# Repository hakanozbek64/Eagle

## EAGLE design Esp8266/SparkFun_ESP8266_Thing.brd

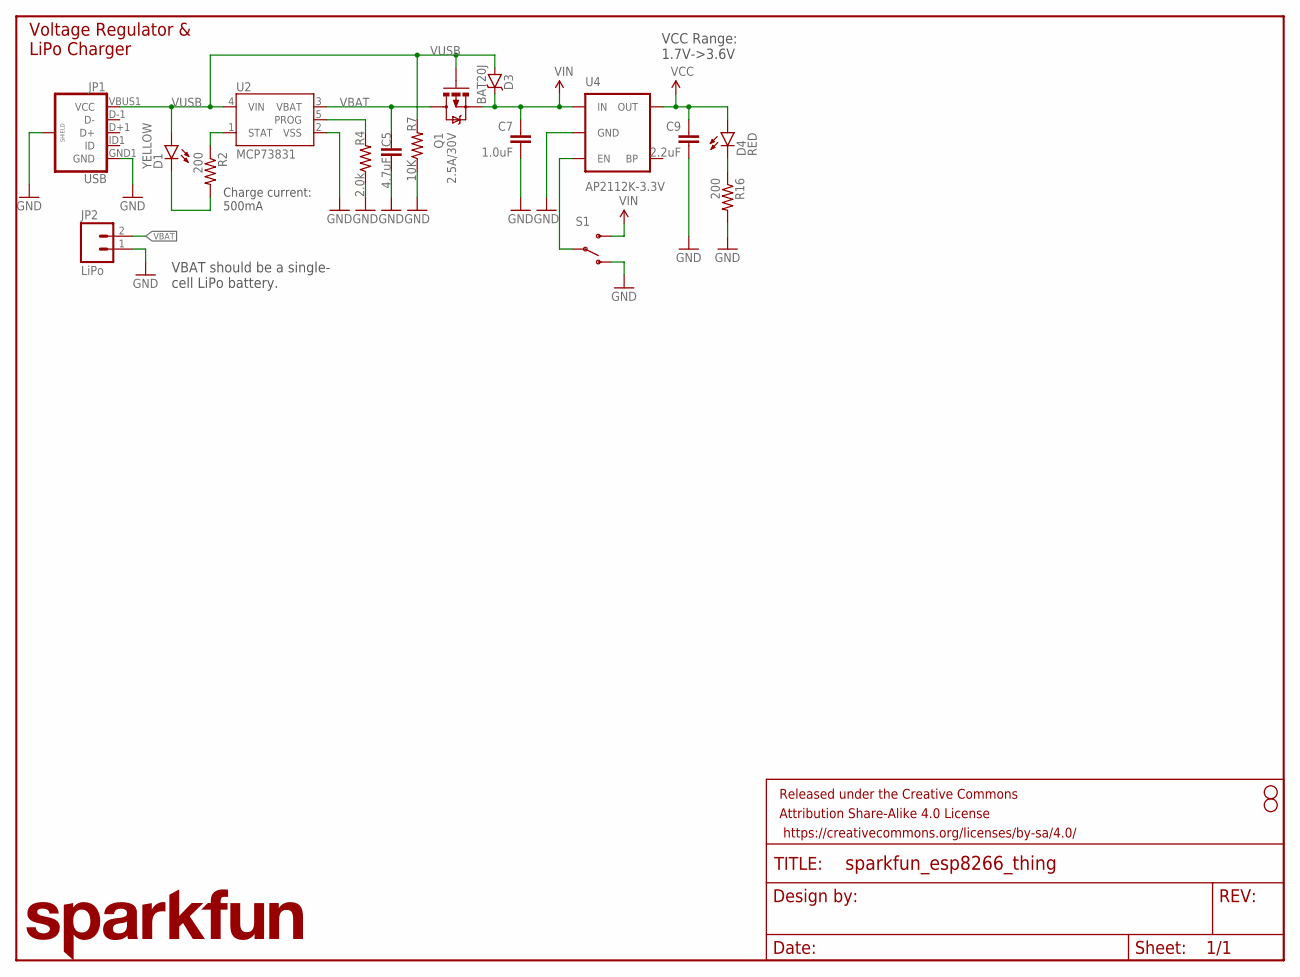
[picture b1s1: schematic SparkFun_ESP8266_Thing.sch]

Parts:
C5: 4.7uF; 0603-CAP
C7: 1.0uF; 0805
C9: 2.2uF; 0603-CAP
D1: YELLOW; LED-0603
D3: BAT20J; SOD-323
D4: RED; LED-0603
FRAME1: FRAME-LETTER; CREATIVE_COMMONS
JP1: USB; USB-B-MICRO-SMD_V03
JP2: LiPo; JST-2-PTH
LOGO1: SFE_LOGO_NAME.2_INCH; SFE_LOGO_NAME_.2
Q1: 2.5A/30V; SOT23-3
R2, R16: 200; 0603-RES
R4: 2.0k; 0603-RES
R7: 10K; 0603-RES
S1: SWITCH-SPDT-SMD-A; SWITCH-SPST-SMD-A
STANDOFF3, STANDOFF4: STAND-OFF
U2: MCP73831; SOT23-5
U4: AP2112K-3.3V; SOT23-5

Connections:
GND: C5.2, C7.2, C9.2, JP1.GND1 (GND), JP1.SHIELD1 (SHIELD), JP1.SHIELD2 (SHIELD), JP1.SHIELD3 (SHIELD), JP2.1, R4.1, R7.1, R16.2, S1.1 (O), U2.2 (VSS), U4.2 (GND)
unnamed: D4.C, R16.1
unnamed: S1.2, U4.3 (EN)
unnamed: R4.2, U2.5 (PROG)
unnamed: D1.C, R2.2
unnamed: R2.1, U2.1 (STAT)
VBAT: C5.1, JP2.2, Q1.3 (D), U2.3 (VBAT)
VCC: C9.1, D4.A, U4.5 (OUT)
VIN: C7.1, D3.C, Q1.2 (S), S1.3 (S), U4.1 (IN)
VUSB: D1.A, D3.A, JP1.VBUS1 (VCC), Q1.1 (G), R7.2, U2.4 (VIN)

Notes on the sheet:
Voltage Regulator & LiPo Charger
VCC Range: 1.7V->3.6V
VBAT should be a single- cell LiPo battery.
Charge current: 500mA

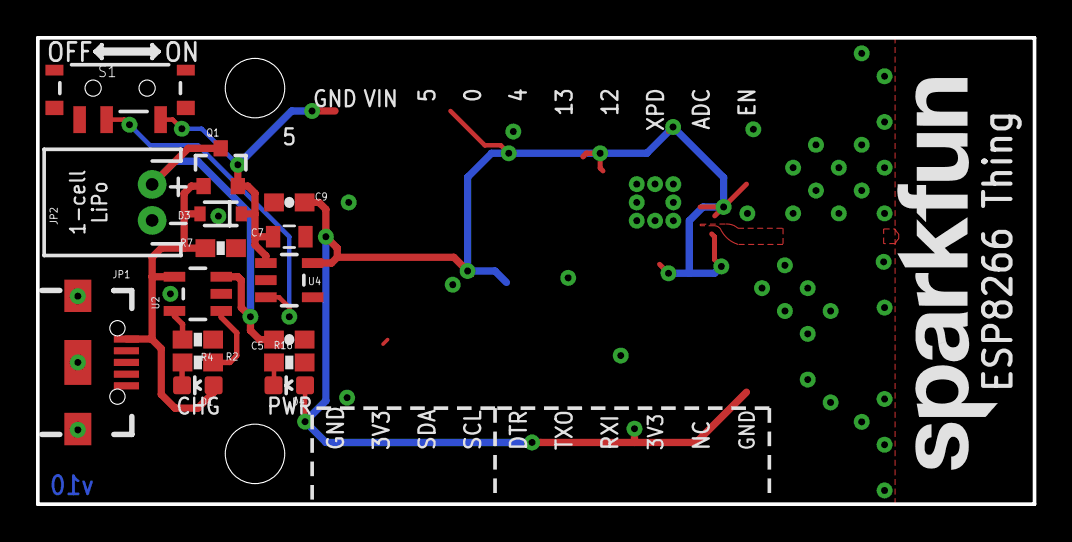
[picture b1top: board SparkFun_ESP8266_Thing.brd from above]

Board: 2 copper layers, 55.4 x 25.9 mm, 21 parts (1 on the bottom side), 10 nets.

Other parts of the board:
LOGO5: SFE_LOGO_NAME.2_INCH; SFE_LOGO_NAME_.2

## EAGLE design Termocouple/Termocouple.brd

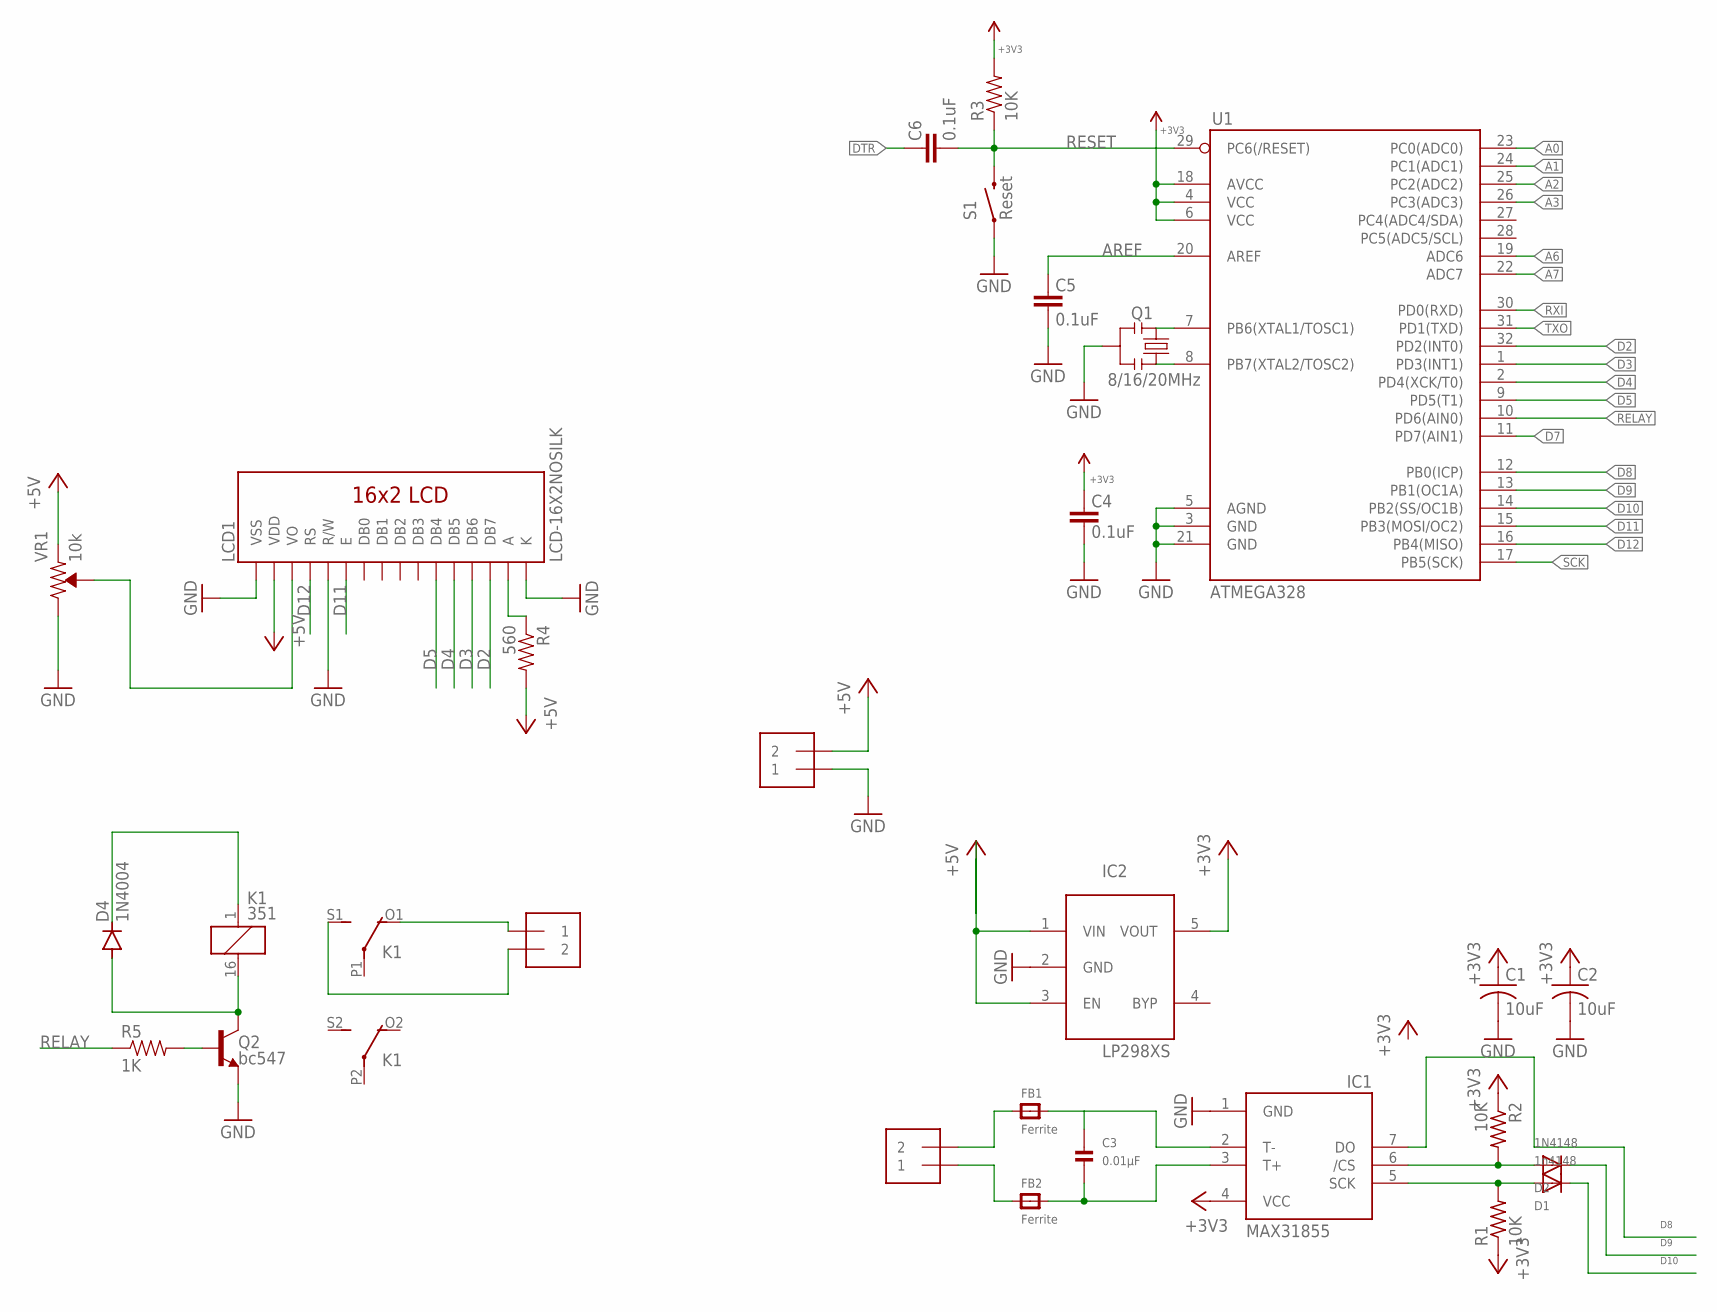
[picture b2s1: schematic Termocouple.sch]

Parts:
C1, C2: 10uF; C0805K
C3: 0.01µF; _0805
C4, C5, C6: 0.1uF; 0603-CAP
D1: 1n4148; SOD-323F
D2: 1N4148; SOD-323F
D4: 1N4004; DO41-10
FB1, FB2: Ferrite; _0805
IC1: MAX31855; SO08
IC2: LP298XS; SOT23-5L
J1, J2, J3: 1X2-3.5MM
K1: 351
LCD1: LCD-16X2NOSILK; LCD-16X2_NOSILK
Q1: 8/16/20MHz; RESONATOR-SMD-1:1
Q2: bc547; SOT23-3
R1, R2: 10K; R0805
R3: 10K; 0805
R4: 560; 0805
R5: 1K; 0805
S1: Reset; TACTILE-SWITCH-SMD-ALT01
U1: ATMEGA328; TQFP32-08
VR1: 10k; TRIMPOT-SMD-3MM-CLOSED

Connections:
+3V3: C1.1, C2.1, C4.2, IC1.4 (VCC), IC2.5 (VOUT), R1.1, R2.1, R3.2, U1.4 (VCC), U1.6 (VCC), U1.18 (AVCC)
+5V: IC2.1 (VIN), IC2.3 (EN), J2.2, LCD1.2 (VDD), R4.2, VR1.1 (CCW)
A0: U1.23 (PC0(ADC0))
A1: U1.24 (PC1(ADC1))
A2: U1.25 (PC2(ADC2))
A3: U1.26 (PC3(ADC3))
A6: U1.19 (ADC6)
A7: U1.22 (ADC7)
AREF: C5.2, U1.20 (AREF)
CS: D2.A, IC1.6 (/CS), R2.2
D2: LCD1.14 (DB7), U1.32 (PD2(INT0))
D3: LCD1.13 (DB6), U1.1 (PD3(INT1))
D4: LCD1.12 (DB5), U1.2 (PD4(XCK/T0))
D5: LCD1.11 (DB4), U1.9 (PD5(T1))
D7: U1.11 (PD7(AIN1))
D8: IC1.7 (DO), U1.12 (PB0(ICP))
D9: D2.C, U1.13 (PB1(OC1A))
D10: D1.C, U1.14 (PB2(SS/OC1B))
D11: LCD1.6 (E), U1.15 (PB3(MOSI/OC2))
D12: LCD1.4 (RS), U1.16 (PB4(MISO))
DTR: C6.2
GND: C1.2, C2.2, C4.1, C5.1, IC1.1 (GND), IC2.2 (GND), J2.1, LCD1.1 (VSS), LCD1.5 (R/W), LCD1.16 (K), Q1.2, Q2.2 (E), S1.1, S1.2 (1), U1.3 (GND), U1.5 (AGND), U1.21 (GND), VR1.3 (CW)
unnamed: FB1.1, J1.2
unnamed: LCD1.15 (A), R4.1
unnamed: LCD1.3 (VO), VR1.2 (WIPER)
unnamed: C3.1, FB1.2, IC1.2 (T-)
unnamed: FB2.1, J1.1
unnamed: C3.2, FB2.2, IC1.3 (T+)
unnamed: Q1.3, U1.8 (PB7(XTAL2/TOSC2))
unnamed: Q1.1, U1.7 (PB6(XTAL1/TOSC1))
unnamed: D4.C, K1.1
unnamed: D4.A, K1.16 (2), Q2.3 (C)
unnamed: Q2.1 (B), R5.2
unnamed: J3.2, K1.S1 (S)
unnamed: J3.1, K1.O1 (O)
RELAY: R5.1, U1.10 (PD6(AIN0))
RESET: C6.1, R3.1, S1.3 (2), S1.4 (2), U1.29 (PC6(/RESET))
RXI: U1.30 (PD0(RXD))
SCK: D1.A, IC1.5 (SCK), R1.2, U1.17 (PB5(SCK))
TXO: U1.31 (PD1(TXD))

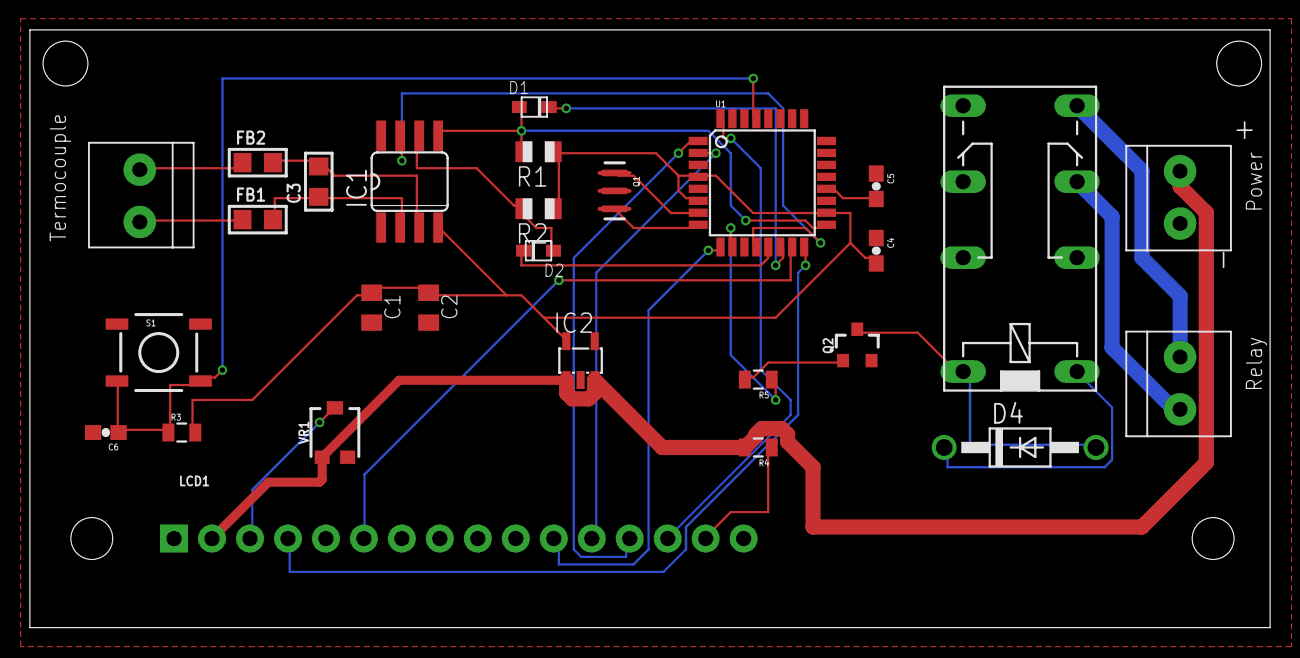
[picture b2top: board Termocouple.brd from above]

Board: 2 copper layers, 82.9 x 40.0 mm, 28 parts (0 on the bottom side), 30 nets.

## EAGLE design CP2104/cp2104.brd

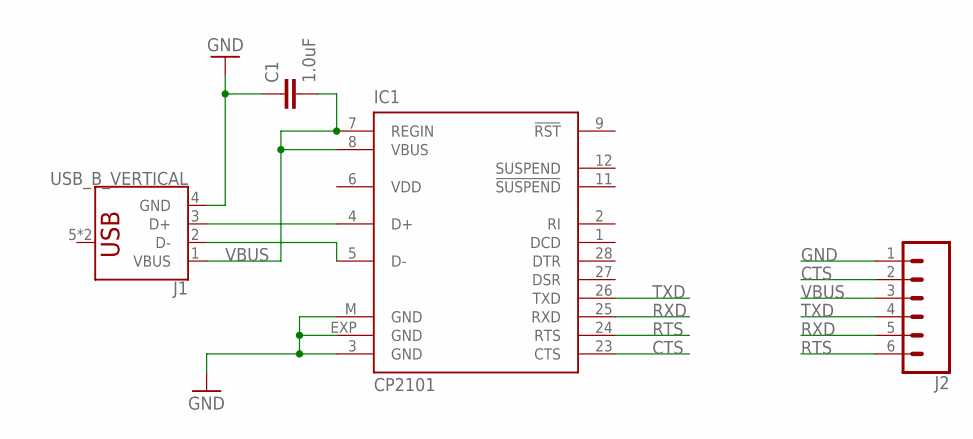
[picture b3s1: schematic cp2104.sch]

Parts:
C1: 1.0uF; 0805
IC1: CP2101; MLP28
J1: USB_B_VERTICAL; USB_B_VERTICAL_PTH
J2: CONN_06NO_SILK_FEMALE_PTH; 1X06_NO_SILK

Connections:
CTS: IC1.23 (CTS), J2.2
GND: C1.1, IC1.3 (GND), IC1.EXP (GND), IC1.M (GND), J1.4 (GND), J2.1
unnamed: IC1.5 (D-), J1.2 (D-)
unnamed: IC1.4 (D+), J1.3 (D+)
RTS: IC1.24 (RTS), J2.6
RXD: IC1.25 (RXD), J2.5
TXD: IC1.26 (TXD), J2.4
VBUS: C1.2, IC1.7 (REGIN), IC1.8 (VBUS), J1.1 (VBUS), J2.3
VDD: IC1.6 (VDD)

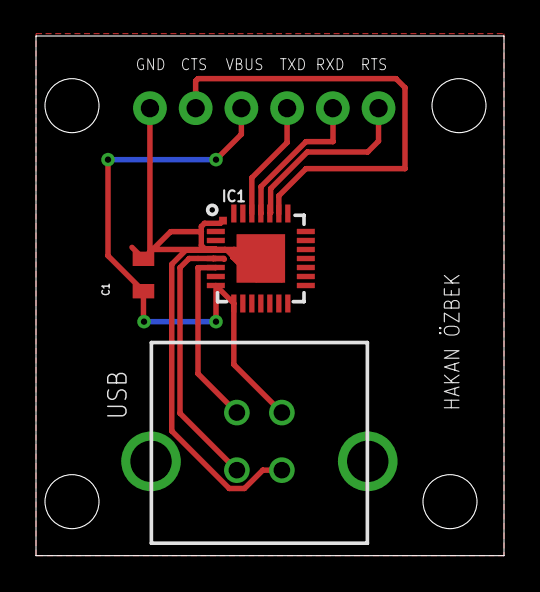
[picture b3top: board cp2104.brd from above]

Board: 2 copper layers, 26.0 x 28.9 mm, 4 parts (0 on the bottom side), 8 nets.

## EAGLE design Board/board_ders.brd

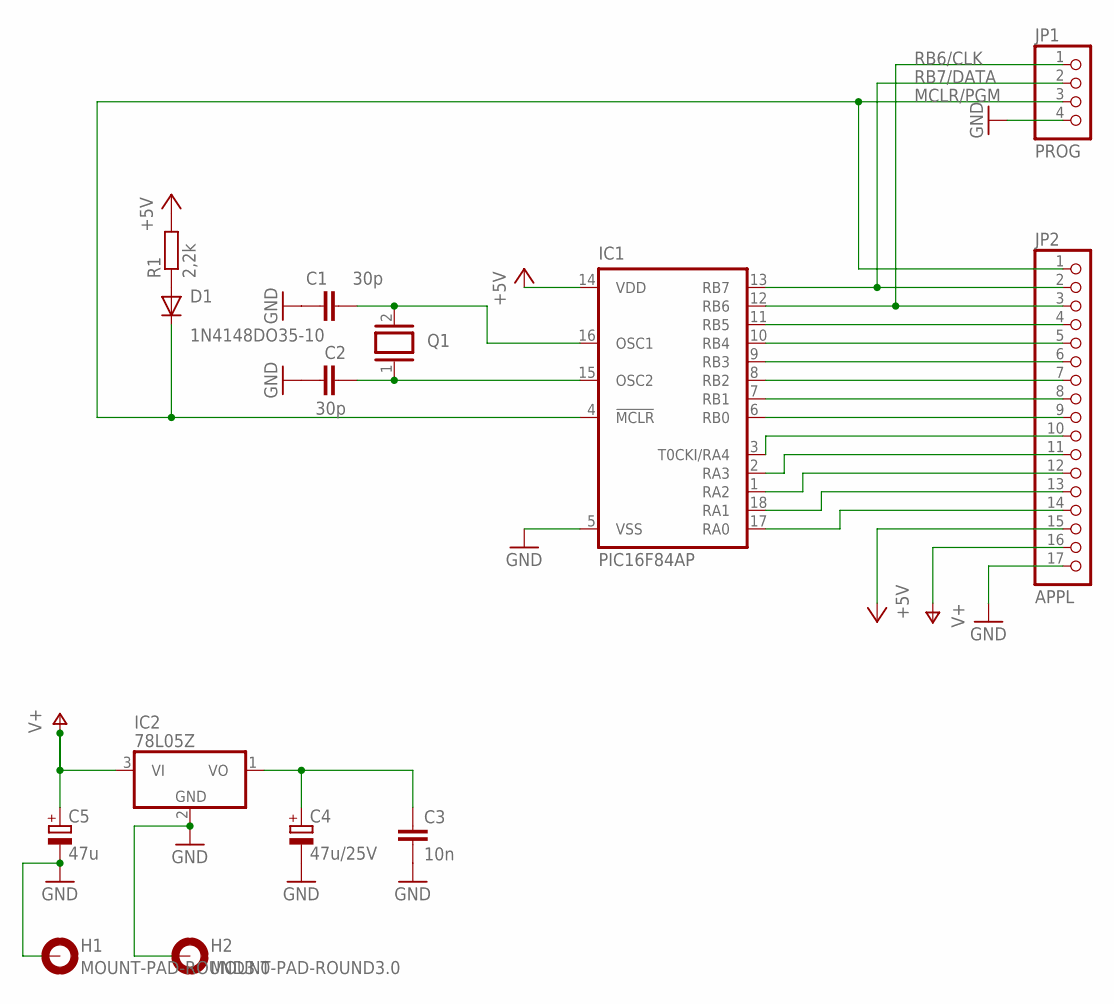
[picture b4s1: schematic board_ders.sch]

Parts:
C1, C2: 30p; C1206
C3: 10n; C025-025X050
C4: 47u/25V; TAP5-45
C5: 47u; TAP5-45
D1: 1N4148DO35-10; DO35-10
H1, H2: MOUNT-PAD-ROUND3.0; 3,0-PAD
IC1: PIC16F84AP; DIL18
IC2: 78L05Z; TO92
JP1: PROG; 1X04
JP2: APPL; 1X17
Q1: XTAL/S; QS
R1: 2,2k; R1206

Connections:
+5V: IC1.14 (VDD), JP2.15, R1.2
GND: C1.1, C2.1, C3.2, C4.-, C5.-, H1.B3,0, H2.B3,0, IC1.5 (VSS), IC2.2 (GND), JP1.4, JP2.17
MCLR/PGM: D1.C, IC1.4 (!MCLR), JP1.3, JP2.1
unnamed: C3.1, C4.+, IC2.1 (VO)
unnamed: C1.2, IC1.16 (OSC1), Q1.2
unnamed: C2.2, IC1.15 (OSC2), Q1.1
unnamed: D1.A, R1.1
RA0: IC1.17 (RA0), JP2.14
RA1: IC1.18 (RA1), JP2.13
RA2: IC1.1 (RA2), JP2.12
RA3: IC1.2 (RA3), JP2.11
RA4: IC1.3 (T0CKI/RA4), JP2.10
RB0: IC1.6 (RB0), JP2.9
RB1: IC1.7 (RB1), JP2.8
RB2: IC1.8 (RB2), JP2.7
RB3: IC1.9 (RB3), JP2.6
RB4: IC1.10 (RB4), JP2.5
RB5: IC1.11 (RB5), JP2.4
RB6/CLK: IC1.12 (RB6), JP1.1, JP2.3
RB7/DATA: IC1.13 (RB7), JP1.2, JP2.2
V+: C5.+, IC2.3 (VI), JP2.16

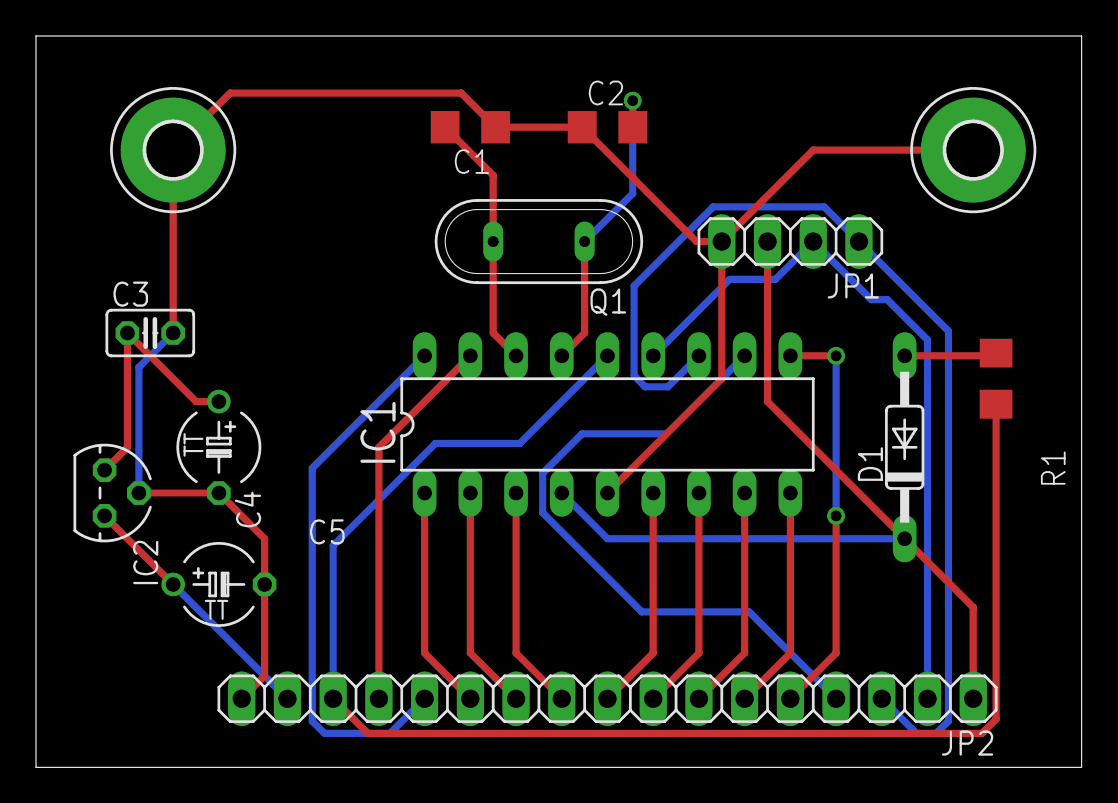
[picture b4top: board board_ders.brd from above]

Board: 2 copper layers, 58.1 x 40.6 mm, 14 parts (0 on the bottom side), 21 nets.

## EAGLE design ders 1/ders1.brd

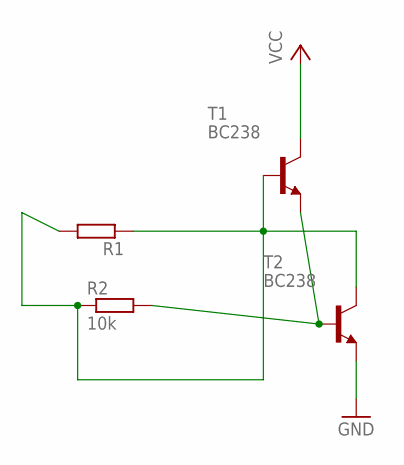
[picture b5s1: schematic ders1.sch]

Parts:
R1: R; R0805
R2: 10k; R0805
T1, T2: BC238; TO92

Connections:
GND: T2.1 (E)
unnamed: R2.2, T1.1 (E), T2.2 (B)
unnamed: R1.1, R1.2, R2.1, T1.2 (B), T2.3 (C)
VCC: T1.3 (C)

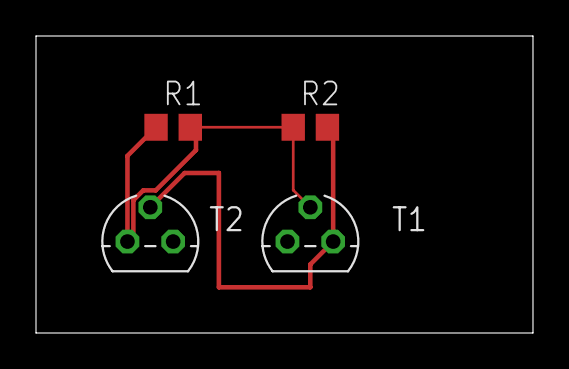
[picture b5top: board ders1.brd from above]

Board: 2 copper layers, 27.6 x 16.5 mm, 4 parts (0 on the bottom side), 2 nets.

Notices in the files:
parts and their libraries:
SparkFun-Capacitors: Licensing: Creative Commons ShareAlike 4.0 International - https://creativecommons.org/licenses/by-sa/4.0
SparkFun-Aesthetics: Released under the Creative Commons Attribution Share-Alike 4.0 License
SparkFun-Aesthetics: https://creativecommons.org/licenses/by-sa/4.0
